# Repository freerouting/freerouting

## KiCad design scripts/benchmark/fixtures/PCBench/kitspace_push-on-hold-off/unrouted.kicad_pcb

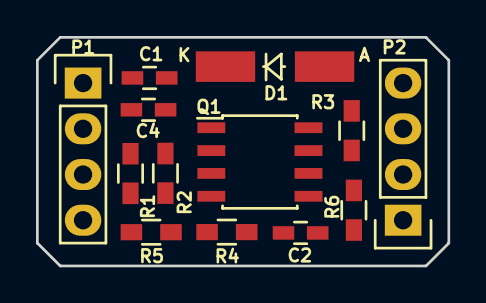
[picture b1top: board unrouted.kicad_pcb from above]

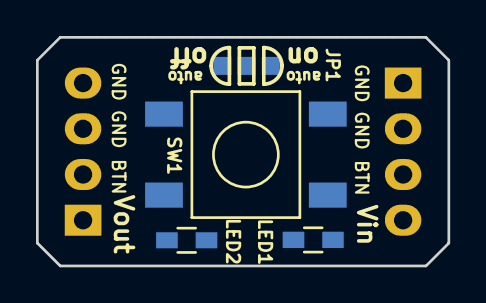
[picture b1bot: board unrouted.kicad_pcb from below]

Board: 2 copper layers, 22.9 x 12.7 mm, 17 parts (4 on the bottom side), 9 nets, no tracks yet.

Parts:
C1: 1uF; C_0603_HandSoldering
C2: 10uF; C_0603_HandSoldering
C4: 0.1uF; C_0603_HandSoldering
D1: D; MiniMELF_Handsoldering
JP1: JUMPER3; SOLDER-JUMPER_2-WAY
LED1, LED2: LED; R_0603_HandSoldering
P1, P2: CONN_01X04; Pin_Header_Straight_1x04
Q1: IRF7309IPBF; SOIC-8_3.9x4.9mm_Pitch1.27mm
R1: 10k; R_0603_HandSoldering
R2, R4: 100k; R_0603_HandSoldering
R3: 300k; R_0603_HandSoldering
R5, R6: 1k; R_0603_HandSoldering
SW1: SW_PUSH_SMALL; FSM2JSMA

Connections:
/Button: C1.2, D1.1, P1.3, P2.2, R1.2, SW1.1
/Vin: C4.1, JP1.2, JP1.3, P1.4, Q1.3, R1.1, R2.1, R5.1
/Vout: C2.2, P2.1, Q1.5, Q1.6, R4.1, R6.1
GND: JP1.1, LED1.1, LED2.1, P1.1, P1.2, P2.3, P2.4, Q1.1, SW1.2
unnamed: C1.1, C4.2, Q1.4, Q1.7, Q1.8, R2.2
unnamed: C2.1, Q1.2, R3.2
unnamed: D1.2, R3.1, R4.2
unnamed: LED1.2, R5.2
unnamed: LED2.2, R6.2

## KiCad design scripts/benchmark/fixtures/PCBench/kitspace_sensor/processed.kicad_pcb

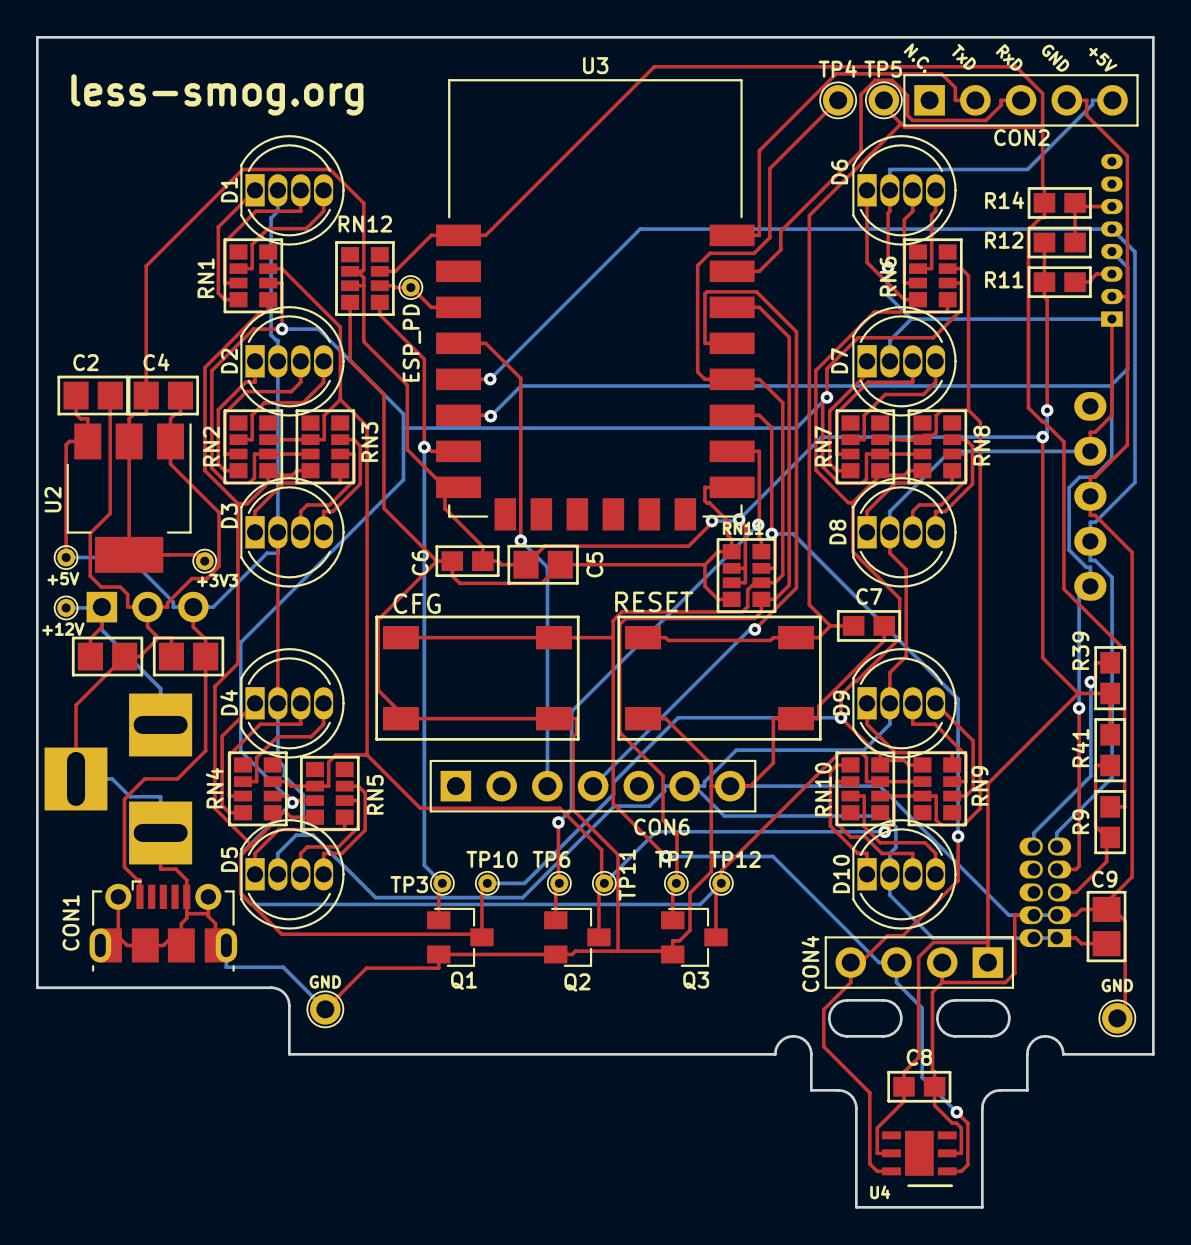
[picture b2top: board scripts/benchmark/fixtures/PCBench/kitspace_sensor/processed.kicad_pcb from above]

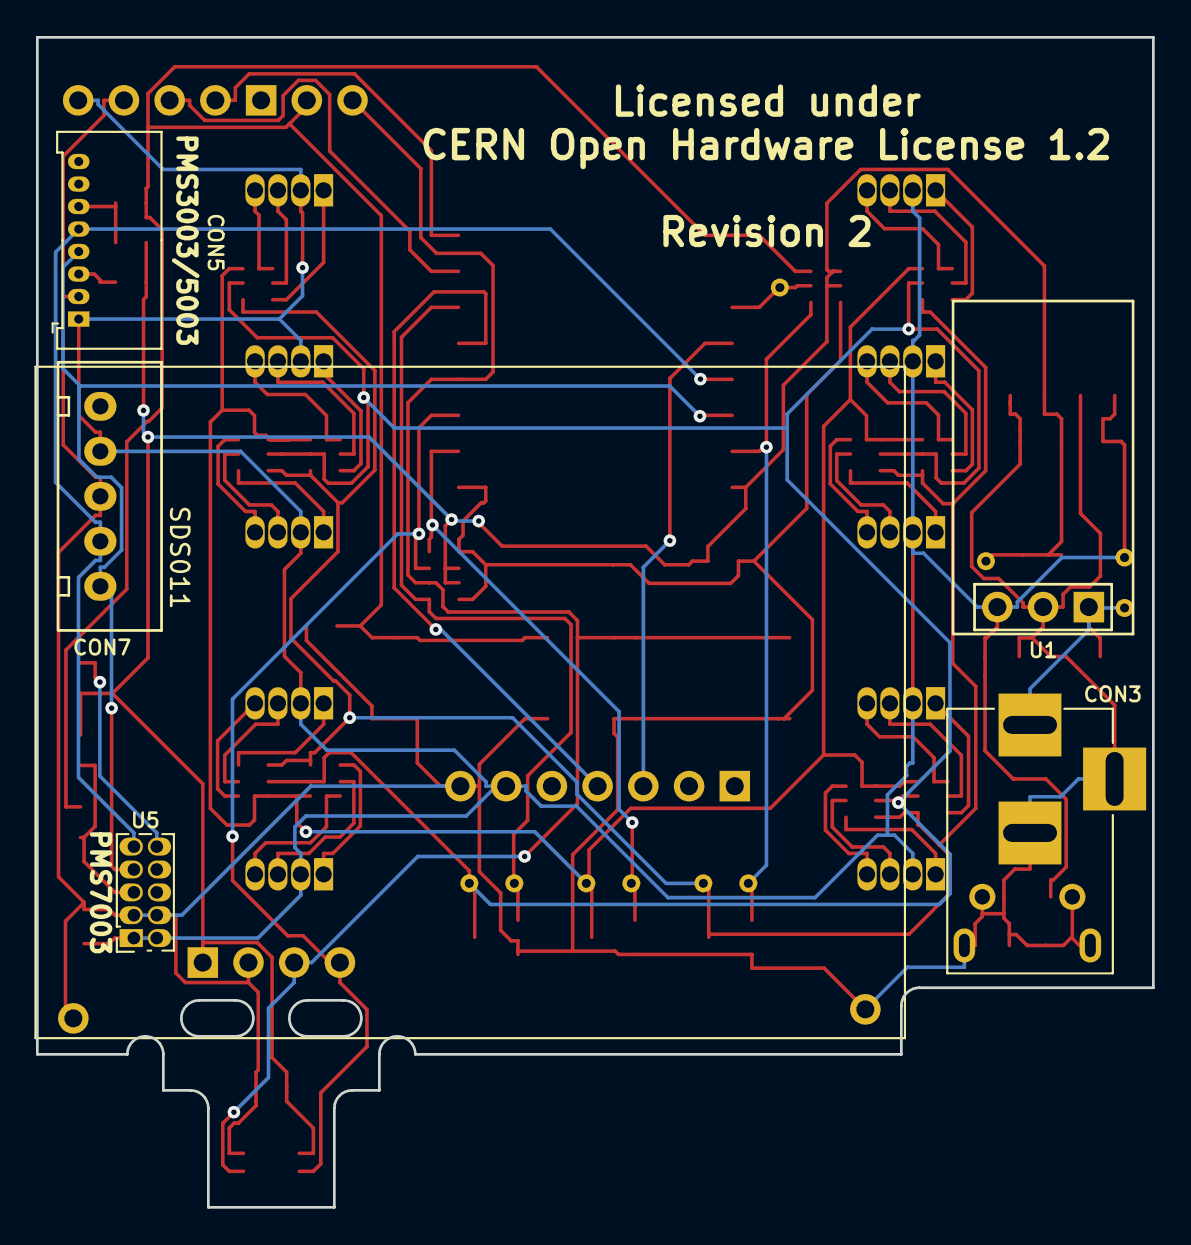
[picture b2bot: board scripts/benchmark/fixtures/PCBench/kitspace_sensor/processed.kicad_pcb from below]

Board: 2 copper layers, 62.0 x 65.0 mm, 68 parts (5 on the bottom side), 54 nets.

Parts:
C1, C3: N.C.; 0805_M
C2, C4, C5, C9: 10uF/10V; 0805_M
C6, C7, C8: 100nF; 0603_M
CON1: Micro USB; USB_Micro-B_Molex-105017-0001
CON2: PROG; Pin_Header_Straight_1x05_Pitch2.54mm
CON3: N.C.; BARREL_JACK
CON4: HTU21D; HTU21D_module
CON5: PMS3003/5003; Molex_PicoBlade_53048-0810
CON6: AUX; E45-TTL-1W
CON7: SDS011; B5B-XH-A(LF)(SN)
D1, D2, D3, D4, D5, D6, D7, D8, D9, D10: RGB 5mm; LED_D5.0mm-4
Q1, Q2, Q3: BSS214N; SOT-23
R9, R11, R12, R14: N.C.; 0603_R_M
R39, R41: 10k; 0603_R_M
RN1, RN2, RN3, RN4, RN5, RN6, RN7, RN8, RN9, RN10: 150R; 4x0603_M
RN11, RN12: 10k; 4x0603_M
SW1: RESET; MicroswitchSmd-4.3_N
SW2: CFG; MicroswitchSmd-4.3_N
TP1: ESP_PD; TP_1.0_0.5_THT
TP2, TP14: GND; TP_1.7_1.0_THT
TP3, TP6, TP7, TP10, TP11, TP12: -; TP_1.0_0.5_THT
TP4: CFG; TP_1.7_1.0_THT
TP5: RESET; TP_1.7_1.0_THT
TP8: +5V; TP_1.0_0.5_THT
TP9: +12V; TP_1.0_0.5_THT
TP13: +3V3; TP_1.0_0.5_THT
U1: N.C.; 5V_DC_DC
U2: TLV1117LV33DCY; SOT-223-3Lead_TabPin2
U3: ESP-12F
U4: HTU21D
U5: PMS7003; PMS7003_THT

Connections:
+3V3: C4.1, C5.1, C6.1, C8.1, CON4.1, R11.2, R12.2, R39.1, R41.1, RN11.2, RN11.3, RN12.2, RN12.3, TP13.1, U2.2, U3.8, U4.5
+5V: C2.1, C3.1, C9.1, CON1.1, CON2.5, CON5.1, CON6.6, CON7.4, D1.2, D2.2, D3.2, D4.2, D5.2, D6.2, D7.2, D8.2, D9.2, D10.2, TP8.1, U1.3, U2.3, U5.1, U5.2
+12V: C1.1, CON3.1, TP9.1, U1.1
/ESP_PD: RN12.6, TP1.1, U3.3
/LED_B: Q3.3, RN1.2, RN2.2, RN3.7, RN4.2, RN5.7, RN6.2, RN7.2, RN8.7, RN9.2, RN10.7, TP12.1
/LED_G: Q2.3, RN1.3, RN2.3, RN3.6, RN4.3, RN5.6, RN6.3, RN7.3, RN8.6, RN9.3, RN10.6, TP11.1
/LED_R: Q1.3, RN1.1, RN2.1, RN3.8, RN4.1, RN5.8, RN6.1, RN7.1, RN8.8, RN9.1, RN10.8, TP10.1
ESP_RXD: CON2.3, U3.21
ESP_TXD: CON2.2, U3.22
GND: C1.2, C2.2, C3.2, C4.2, C5.2, C6.2, C7.2, C8.2, C9.2, CON1.5, CON1.6, CON2.4, CON3.2, CON3.3, CON4.2, CON5.2, CON6.7, CON7.3, Q1.2, Q2.2, Q3.2, RN11.1, RN11.4, RN12.4, SW1.2, SW2.2, TP2.1, TP14.1, U1.2, U2.1, U3.15, U4.2, U5.3, U5.4
GPIO4: CON6.4, U3.19
GPIO16: CON6.3, U3.4
HTU_SCL: CON4.4, RN11.7, U3.17, U4.6
HTU_SDA/CFG_BTN: CON4.3, RN11.6, SW2.1, TP4.1, U3.18, U4.1
LED_B_CTRL: Q3.1, RN11.5, TP7.1, U3.20
LED_G_CTRL: Q2.1, RN11.8, TP6.1, U3.16
LED_R_CTRL: Q1.1, RN12.5, TP3.1, U3.7
unnamed: CON5.3, R11.1
unnamed: CON5.6, R12.1, R14.1
unnamed: D1.1, RN1.8
unnamed: D1.3, RN1.7
unnamed: D1.4, RN1.6
unnamed: D2.1, RN2.8
unnamed: D2.3, RN2.7
unnamed: D2.4, RN2.6
unnamed: D3.1, RN3.1
unnamed: D3.3, RN3.2
unnamed: D3.4, RN3.3
unnamed: D4.1, RN4.8
unnamed: D4.3, RN4.7
unnamed: D4.4, RN4.6
unnamed: D5.1, RN5.1
unnamed: D5.3, RN5.2
unnamed: D5.4, RN5.3
unnamed: D6.1, RN6.8
unnamed: D6.3, RN6.7
unnamed: D6.4, RN6.6
unnamed: D7.1, RN7.8
unnamed: D7.3, RN7.7
unnamed: D7.4, RN7.6
unnamed: D8.1, RN8.1
unnamed: D8.3, RN8.2
unnamed: D8.4, RN8.3
unnamed: D9.1, RN9.8
unnamed: D9.3, RN9.7
unnamed: D9.4, RN9.6
unnamed: D10.1, RN10.1
unnamed: D10.3, RN10.2
unnamed: D10.4, RN10.3
unnamed: R39.2, U5.10
unnamed: R9.1, R41.2, U5.5
PMS_RXD: CON5.4, CON7.1, U3.6, U5.7
PMS_TXD: CON5.5, CON7.2, U3.5, U5.9
RESET: C7.1, R9.2, R14.2, RN12.7, SW1.1, TP5.1, U3.1

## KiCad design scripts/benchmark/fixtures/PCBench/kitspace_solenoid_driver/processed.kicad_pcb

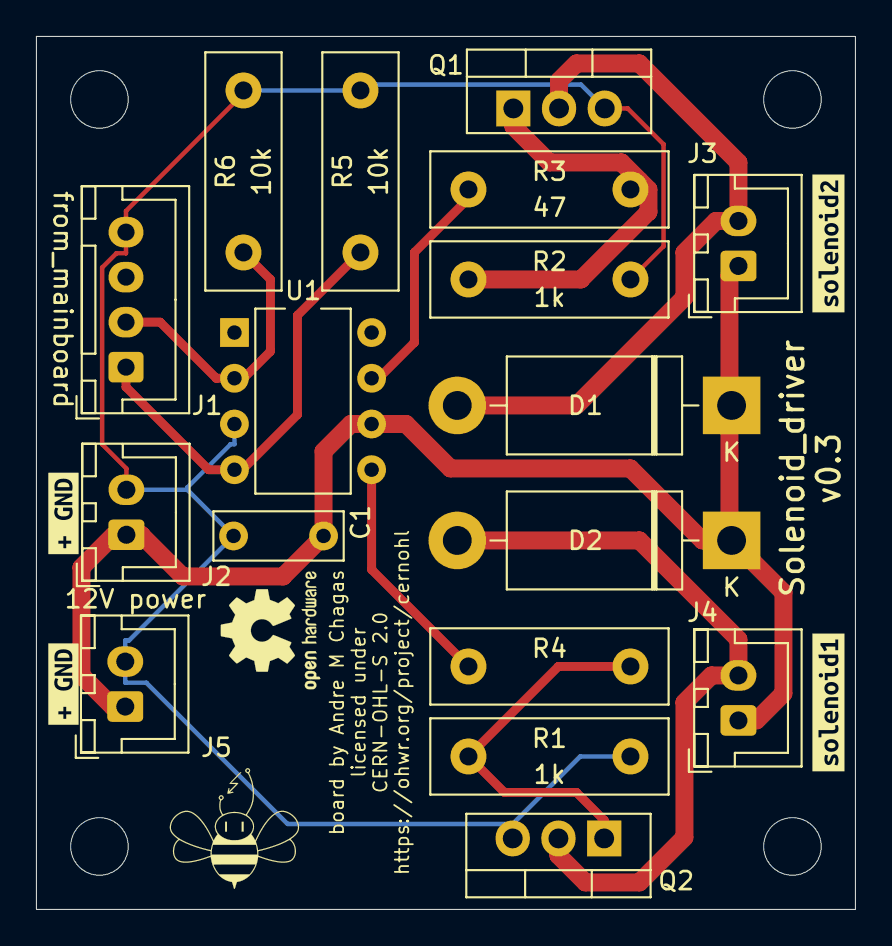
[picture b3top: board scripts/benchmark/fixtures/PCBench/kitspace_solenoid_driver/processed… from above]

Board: 2 copper layers, 45.5 x 48.5 mm, 26 parts (0 on the bottom side), 10 nets.

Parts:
C1: 100nF; C_Disc_D7.0mm_W2.5mm_P5.00mm
D1, D2: D_Schottky; D_DO-201AD_P15.24mm_Horizontal
J1: from_mainboard; JST_XH_B4B-XH-A_1x04_P2.50mm_Vertical
J2, J5: 12V power; JST_XH_B2B-XH-A_1x02_P2.50mm_Vertical
J3: to_solenoid2; JST_XH_B2B-XH-A_1x02_P2.50mm_Vertical
J4: to_solenoid1; JST_XH_B2B-XH-A_1x02_P2.50mm_Vertical
Q1, Q2: Q_NMOS_GDS; TO-220-3_Vertical
R1, R2: 1k; R_Box_L13.0mm_W4.0mm_P9.00mm
R3, R4: 47; R_Box_L13.0mm_W4.0mm_P9.00mm
R5, R6: 10k; R_Box_L13.0mm_W4.0mm_P9.00mm
REF1, REF2, REF3, REF4: MountingHole_3.2mm_M3_DIN965
REF5: OSHW-Logo2_7.3x6mm_SilkScreen
U1: MIC4427; DIP-8_W7.62mm
kibuzzard-63063C94: G***; kibuzzard-63063C94
kibuzzard-63064E8E: G***; kibuzzard-63064E8E
kibuzzard-63064EFA: G***; kibuzzard-63064EFA
kibuzzard-63065932: G***; kibuzzard-63065932

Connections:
+12V: C1.1, D1.1, D2.1, J2.1, J3.1, J4.1, J5.1, U1.6
GND: C1.2, J1.4, J2.2, J5.2, Q1.3, Q2.3, R1.1, R2.1, R5.1, R6.1, U1.3
unnamed: D1.2, J3.2, Q1.2
unnamed: D2.2, J4.2, Q2.2
unnamed: J1.1, R5.2, U1.4
unnamed: Q1.1, R2.2, R3.1
unnamed: Q2.1, R1.2, R4.1
unnamed: J1.2, R6.2, U1.2
solenoid1: R3.2, U1.7
solenoid2: R4.2, U1.5

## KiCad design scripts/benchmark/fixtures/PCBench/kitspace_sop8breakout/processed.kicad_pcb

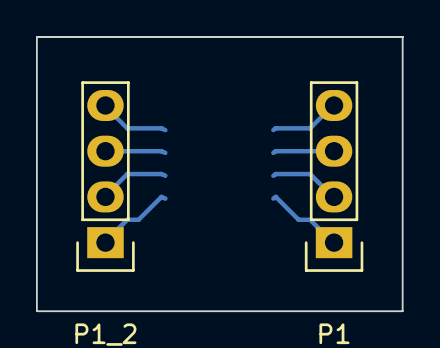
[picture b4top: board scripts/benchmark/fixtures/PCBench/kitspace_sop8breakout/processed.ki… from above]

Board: 2 copper layers, 20.3 x 15.2 mm, 3 parts (1 on the bottom side), 8 nets.

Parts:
IC1: MCP6002; SOP-8
P1, P1_2: CONN_01X04; Pin_Header_Straight_1x04

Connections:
unnamed: IC1.1, P1_2.1
unnamed: IC1.2, P1_2.2
unnamed: IC1.3, P1_2.3
unnamed: IC1.4, P1_2.4
unnamed: IC1.5, P1.4
unnamed: IC1.6, P1.3
unnamed: IC1.7, P1.2
unnamed: IC1.8, P1.1

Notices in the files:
scripts/benchmark/fixtures/PCBench/kitspace_sensor/processed.kicad_pcb:
Licensed under
CERN Open Hardware License 1.2
scripts/benchmark/fixtures/PCBench/kitspace_solenoid_driver/processed.kicad_pcb:
CERN-OHL-S 2.0
